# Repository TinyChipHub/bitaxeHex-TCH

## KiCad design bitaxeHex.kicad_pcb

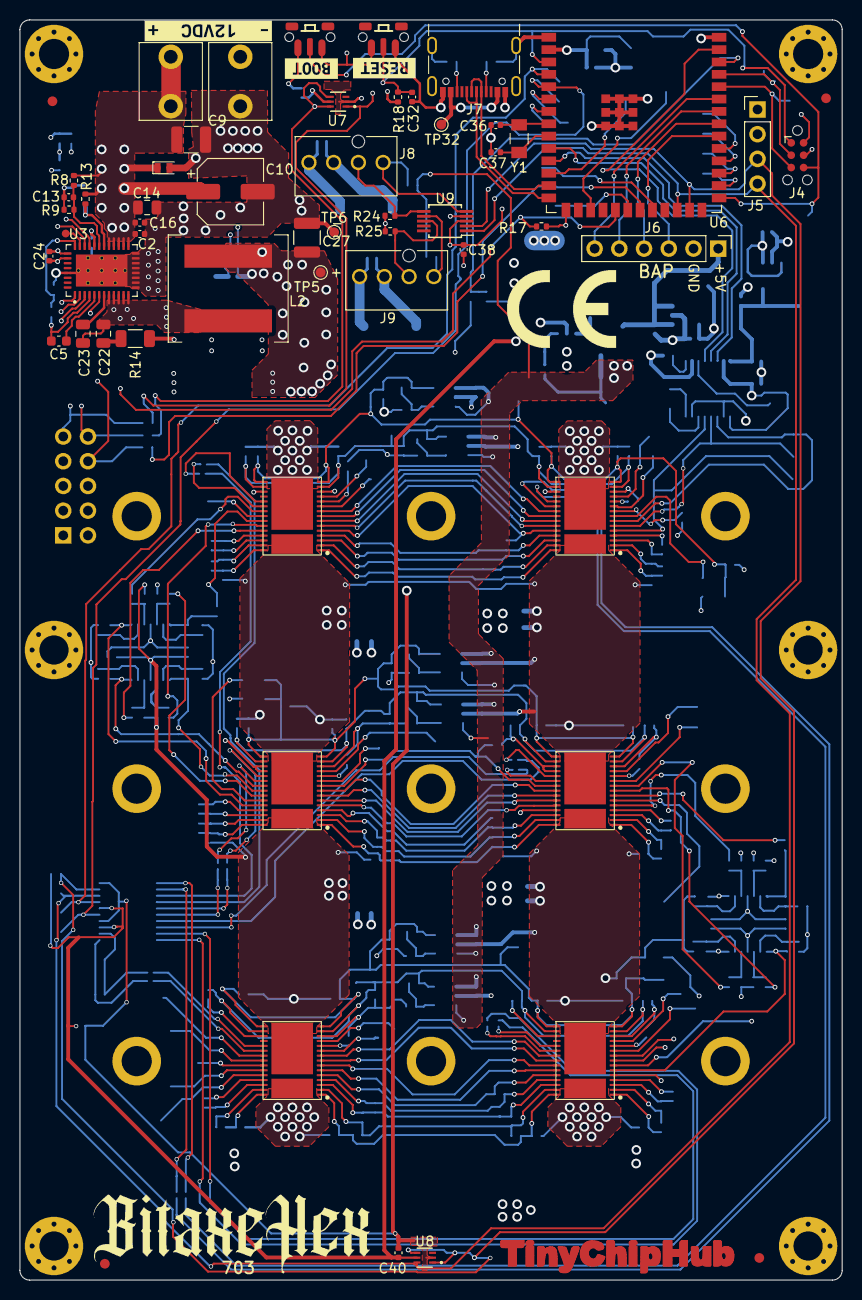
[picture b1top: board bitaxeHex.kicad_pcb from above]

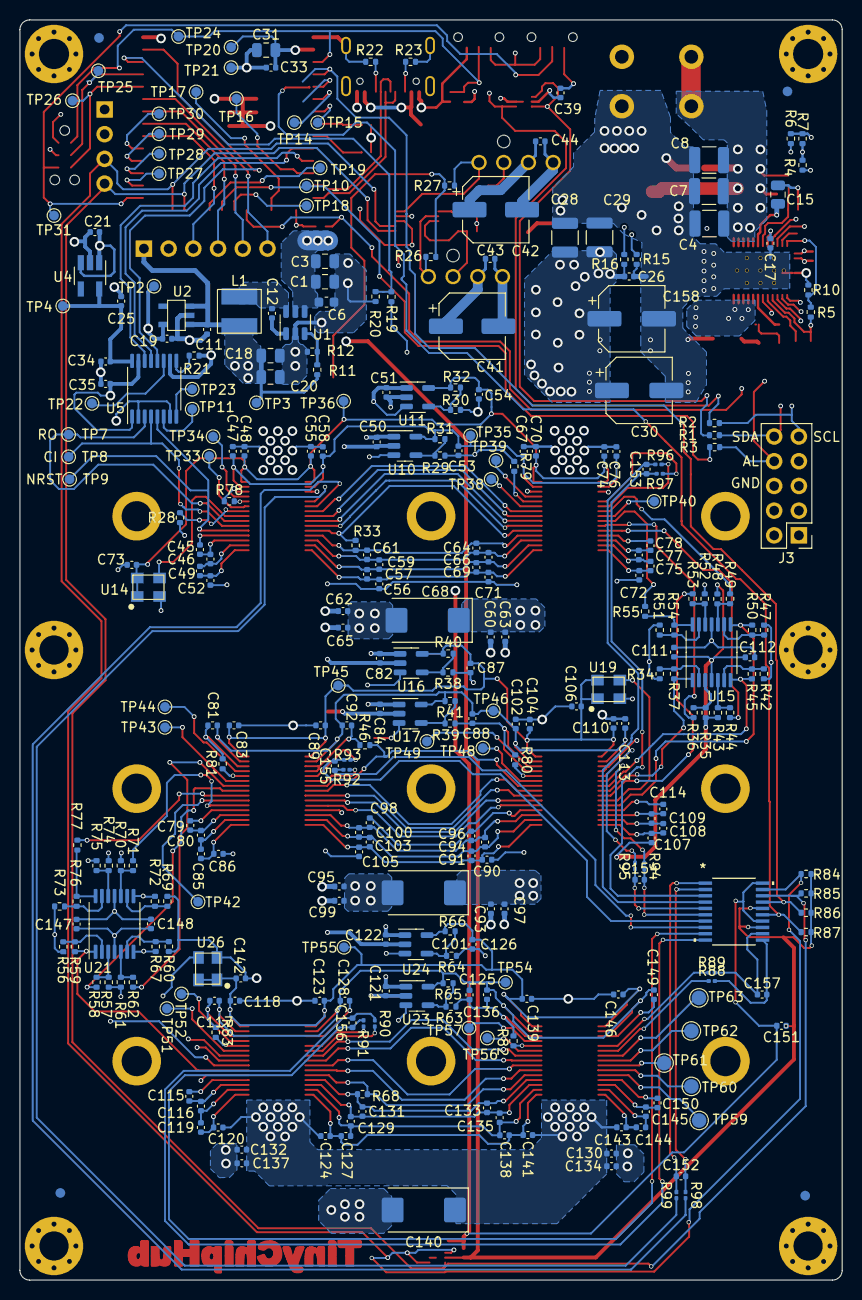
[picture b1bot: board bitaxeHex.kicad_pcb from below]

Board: 4 copper layers, 84.5 x 129.5 mm, 381 parts (306 on the bottom side), 216 nets.

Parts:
C1, C3, C18, C20, C31: 10uF; C_0805_2012Metric
C2: 4.7nF; C_0402_1005Metric
C4, C7, C8, C9: 22uF; C_1210_3225Metric
C5: 1uF; C_0603_1608Metric
C6: 0.1uF; C_0603_1608Metric
C10, C30, C158: 180uF; CP_Elec_6.3x5.9
C11, C19, C21, C25, C32, C45, C46, C47, C48, C49, C52, C53, C54, C55, C56, C57, C58, C59, C61, C63, C64, C65, C66, C67, C69, C70, C71, C72, C74, C75, C76, C77, C78, C79, C80, C81, C83, C85, C86, C87, C88, C89, C90, C91, C92, C94, C96, C97, C98, C99, C100, C102, C103, C104, C105, C107, C108, C109, C110, C112, C113, C114, C115, C116, C117, C118, C119, C120, C123, C124, C125, C126, C127, C128, C129, C131, C133, C134, C135, C136, C137, C138, C139, C141, C143, C144, C145, C146, C148, C149, C150: 1uF; C_0402_1005Metric
C12, C33, C50, C51, C60, C62, C73, C82, C84, C93, C95, C106, C111, C121, C122, C130, C132, C142, C147, C151: 0.1uF; C_0402_1005Metric
C13: 100nF; C_0402_1005Metric
C14, C15: 1uF; C_0805_2012Metric
C16, C26, C152, C153, C154, C155, C156, C157: 2.2nF; C_0402_1005Metric
C17: 4.7uF; C_0402_1005Metric
C22: 1nF; C_0805_2012Metric
C23: 100nF; C_0805_2012Metric
C24: 100pF; C_0402_1005Metric
C27, C28, C29: 47uF; C_1210_3225Metric
C34, C35, C38, C39, C40, C43, C44: 311-3342-1-ND; C_0402_1005Metric
C36, C37: 6.8pF; C_0402_1005Metric
C41, C42: 220uF; CP_Elec_6.3x7.7
C68, C101, C140: 330uF; CP_EIA-7343-31_Kemet-D_Pad2.25x2.55mm_HandSolder
D1: 824045812
FID1, FID2, FID3, FID4, FID5, FID6, FID7, FID8: Fiducial; Fiducial_1mm_Mask2mm
H1, H2, H3, H4, H5, H6: MountingHole; MountingHole_3mm_Pad_Via
H7, H8, H9, H10, H11, H12, H13, H14, H15: HeatsinkMountingHole; 3.1mm_mounting
HS1: Heatsink; hex-heatsink
J1, J2: Conn_01x01; 63862-1
J3: Conn_02x05_Odd_Even; PinHeader_2x05_P2.54mm_Vertical
J4: TC2030-IDC; Tag-Connect_TC2030-IDC-NL_2x03_P1.27mm_Vertical
J5: Conn_01x04; PinHeader_1x04_P2.54mm_Vertical
J6: Conn_01x06; PinHeader_1x06_P2.54mm_Vertical
J7: USB_C_Receptacle_USB2.0; USB_C_Receptacle_GCT_USB4105-xx-A_16P_TopMnt_Horizontal
J8, J9: Conn_01x04; 470531000
L1: 8.2 uH; 74438357082
L2: 680nH; L_Coilcraft_XAL1010-XXX
R1, R2, R3: 0R; R_0402_1005Metric
R4, R5: 17.8K; R_0402_1005Metric
R6, R17, R18, R26, R27, R28, R35, R36, R43, R44, R48, R49, R52, R53, R57, R58, R61, R62, R70, R71, R74, R75: 10k; R_0402_1005Metric
R7: 31.6K; R_0402_1005Metric
R8: 12.7K; R_0402_1005Metric
R9, R16: 1.37K; R_0402_1005Metric
R10: 26.1K; R_0402_1005Metric
R11, R29, R30, R31, R38, R39, R41, R63, R64, R65: 115k; R_0402_1005Metric
R12, R20: 22.1k; R_0402_1005Metric
R13: 10R; R_0402_1005Metric
R14: 1R; R_1206_3216Metric
R15: 49.9R; R_0402_1005Metric
R19: 7.87k; R_0402_1005Metric
R21: 20k; R_0402_1005Metric
R22, R23: 5.1k; R_0402_1005Metric
R24, R25: 5.6k; R_0402_1005Metric
R32, R40, R66: 402k; R_0402_1005Metric
R33, R46, R68: 2k; R_0402_1005Metric
R34, R37, R42, R45, R47, R50, R51, R54, R55, R56, R59, R60, R67, R69, R72, R73, R76, R77, R78, R79, R80, R81, R82, R83: 1k; R_0402_1005Metric
R84, R85, R86, R87: 4.7k; R_0402_1005Metric
R88, R89, R90, R91, R92, R93, R94, R95, R96, R97, R98, R99: 100R; R_0201_0603Metric
SW1, SW2: SWITCH-SPST; TL3340-switch
TP1: TestPoint; TestPoint_Pad_D0.8mm
TP2, TP3, TP4, TP5, TP6, TP7, TP8, TP9, TP10, TP11, TP14, TP15, TP16, TP17, TP18, TP19, TP20, TP21, TP22, TP23, TP24, TP25, TP26, TP27, TP28, TP29, TP30, TP31, TP32, TP33, TP34, TP35, TP36, TP38, TP39, TP40, TP42, TP43, TP44, TP45, TP46, TP48, TP49, TP51, TP52, TP54, TP55, TP56, TP57: TestPoint; TestPoint_Pad_D1.0mm
TP59, TP60, TP61, TP62, TP63: TestPoint; TestPoint_Pad_D1.5mm
U1: LMR54410; SOT-23-6
U2: RT9080-33GJ5
U3: TPS546D24ARVFR; LQFN40-CLIP
U4: MIC5504-MS; SOT-23-5_HandSoldering
U5: SN74AVC4T774; TSSOP-16_4.4x5mm_P0.65mm
U6: ESP32-S3-WROOM-1; ESP32-S3-WROOM-1U
U7, U8: TMP1075; SOT5X3-6_DRL_TEX
U9: EMC2302; MSOP-10_3x3mm_P0.5mm
U10, U11, U16, U17, U23, U24: AP7331; TSOT-23-5
U12, U25, U27, U28: BM1368_mode1; BM1368
U13, U18: BM1368_mode0; BM1368
U14, U19, U26: 25MHz; O 25,0-JO32-B-1V3-1-T1-LF
U15, U21: TLV3544; TSSOP-14_4.4x5mm_P0.65mm
U20: MAX6689UP9A+
Y1: 32.768kHz; SC32S-7PF20PPM
kibuzzard-65356D4E: G***; kibuzzard-65356D4E
kibuzzard-65356D5C: G***; kibuzzard-65356D5C
kibuzzard-65978662: G***; kibuzzard-65978662

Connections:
/1V8: C25.1, C34.2, TP4.1, U4.5 (VOUT), U5.16 (VCCA)
/3V3: C19.1, C21.1, C31.1, C33.1, C35.1, C38.1, C39.1, C40.1, C151.1, J4.2, J5.2, R17.2, R18.1, R24.2, R25.2, R84.2, R85.2, R86.2, R87.2, TP2.1, TP20.1, U2.5 (VOUT), U4.1 (VIN), U4.3 (EN), U5.1 (DIR1), U5.15 (VCCB), U6.2 (3V3), U6.15 (GPIO3/TOUCH3/ADC1_CH2*), U7.5 (V+), U8.5 (V+), U9.3 (VDD), U20.13 (STBY), U20.16 (VCC)
/5V: C11.1, C18.1, C20.1, C50.2, C51.2, C82.2, C84.2, C121.2, C122.2, J6.1, L1.2, R11.1, R26.2, R27.2, TP3.1, U2.1 (VIN), U2.3 (EN), U10.1 (VIN), U10.3 (EN), U11.1 (VIN), U11.3 (EN), U16.1 (VIN), U16.3 (EN), U17.1 (VIN), U17.3 (EN), U23.1 (VIN), U23.3 (EN), U24.1 (VIN), U24.3 (EN)
/BM1368-1/0V8: C47.1, C53.1, C58.1, C67.1, C76.1, R31.2, TP35.1, U10.5 (VOUT), U12.14 (VDDIO_08_0), U12.17 (VDDIO_08_1), U28.14 (VDDIO_08_0), U28.17 (VDDIO_08_1)
/BM1368-1/1V8: C48.1, C54.1, C55.1, C70.1, C73.1, C74.1, R32.1, TP36.1, U11.5 (VOUT), U12.15 (VDDIO_12_0), U12.16 (VDDIO_12_1), U14.1 (EN), U14.4 (VIN), U28.15 (VDDIO_12_0), U28.16 (VDDIO_12_1)
/BM1368-1/BI1: R28.2, U28.9 (BI)
/BM1368-1/BO: R49.1, U12.22 (BO)
/BM1368-1/CLKI1: U14.3 (OUT), U28.8 (CLKI)
/BM1368-1/CO: R36.1, U12.25 (CO)
/BM1368-1/NRSTO: R44.1, U12.26 (NRSTO)
/BM1368-1/RI: R55.1, U12.24 (RI)
/BM1368-1/TEMP_N1: R98.1, U28.21 (TEMP_N)
/BM1368-1/TEMP_N2: R96.1, U12.21 (TEMP_N)
/BM1368-1/TEMP_P1: R99.1, U28.20 (TEMP_P)
/BM1368-1/TEMP_P2: R97.1, U12.20 (TEMP_P)
/BM1368-1/VDD1: C52.2, C56.1, C60.2, C62.2, C63.1, C65.1, C68.1, C71.2, C72.1, C79.1, C81.2, C82.1, C83.2, C84.1, C87.2, C88.2, C89.2, C92.2, C93.1, C95.1, C96.2, C97.2, C98.1, C99.2, C101.2, C102.2, C104.2, C106.2, C110.2, C113.2, C114.2, C147.1, C148.1, R34.2, R38.1, R39.1, R42.2, R46.1, R47.2, R51.2, R74.1, R80.1, R81.1, U12.31 (VDD), U13.4 (VSS), U13.13 (PLL_VSS), U13.18 (VSS), U13.19 (PIN_MODE), U13.27 (VSS), U13.32 (VSS), U16.2 (GND), U17.2 (GND), U18.4 (VSS), U18.13 (PLL_VSS), U18.18 (VSS), U18.19 (PIN_MODE), U18.27 (VSS), U18.32 (VSS), U19.2 (GND), U21.11 (V-), U28.31 (VDD)
/BM1368-2/0V8: C81.1, C88.1, C92.1, C102.1, C113.1, R41.2, TP46.1, U13.14 (VDDIO_08_0), U13.17 (VDDIO_08_1), U17.5 (VOUT), U18.14 (VDDIO_08_0), U18.17 (VDDIO_08_1)
/BM1368-2/1V8: C83.1, C87.1, C89.1, C104.1, C106.1, C110.1, R40.1, TP45.1, U13.15 (VDDIO_12_0), U13.16 (VDDIO_12_1), U16.5 (VOUT), U18.15 (VDDIO_12_0), U18.16 (VDDIO_12_1), U19.1 (EN), U19.4 (VIN)
/BM1368-2/BI2: R50.1, U13.26 (BI), U15.8
/BM1368-2/BO: R71.1, U18.5 (BO)
/BM1368-2/CI2: R37.1, U13.23 (CI), U15.1
/BM1368-2/CLKI2: U13.25 (CLKI), U19.3 (OUT)
/BM1368-2/CO: R58.1, U18.8 (CO)
/BM1368-2/NRSTI2: R45.1, U13.22 (NRSTI), U15.7
/BM1368-2/NRSTO: R62.1, U18.9 (NRSTO)
/BM1368-2/RI: R77.1, U18.7 (RI)
/BM1368-2/RO2: R53.1, U13.24 (RO)
/BM1368-2/TEMP_N3: R94.1, U13.21 (TEMP_N)
/BM1368-2/TEMP_N4: R92.1, U18.21 (TEMP_N)
/BM1368-2/TEMP_P3: R95.1, U13.20 (TEMP_P)
/BM1368-2/TEMP_P4: R93.1, U18.20 (TEMP_P)
/BM1368-2/VDD2: C86.2, C90.1, C93.2, C95.2, C97.1, C99.1, C101.1, C105.2, C107.1, C111.2, C112.2, C115.1, C117.2, C118.2, C121.1, C122.1, C123.2, C125.2, C126.2, C128.2, C130.1, C131.2, C132.1, C133.1, C134.2, C136.2, C137.2, C139.2, C140.2, C142.2, C146.2, C149.2, C150.2, R35.2, R43.1, R48.1, R56.2, R60.2, R63.1, R64.1, R68.1, R69.2, R73.2, R82.1, R83.1, U13.31 (VDD), U15.4 (V+), U18.31 (VDD), U23.2 (GND), U24.2 (GND), U25.4 (VSS), U25.13 (PLL_VSS), U25.18 (VSS), U25.27 (VSS), U25.32 (VSS), U26.2 (GND), U27.4 (VSS), U27.13 (PLL_VSS), U27.18 (VSS), U27.27 (VSS), U27.32 (VSS)
/BM1368-3/0V8: C117.1, C125.1, C128.1, C136.1, C149.1, R65.2, TP54.1, U23.5 (VOUT), U25.14 (VDDIO_08_0), U25.17 (VDDIO_08_1), U27.14 (VDDIO_08_0), U27.17 (VDDIO_08_1)
/BM1368-3/1V8: C118.1, C123.1, C126.1, C139.1, C142.1, C146.1, R66.1, TP55.1, U24.5 (VOUT), U25.15 (VDDIO_12_0), U25.16 (VDDIO_12_1), U26.1 (EN), U26.4 (VIN), U27.15 (VDDIO_12_0), U27.16 (VDDIO_12_1)
/BM1368-3/BI3: R72.1, U21.8, U25.9 (BI)
/BM1368-3/BO3: TP60.1, U27.25 (CO)
/BM1368-3/CI3: R59.1, U21.1, U25.6 (CI)
/BM1368-3/CLKI3: U25.8 (CLKI), U26.3 (OUT)
/BM1368-3/CLKO3: TP62.1, U27.23 (CLKO)
/BM1368-3/CO3: TP63.1, U27.22 (BO)
/BM1368-3/NRSTI3: R67.1, U21.7, U25.5 (NRSTI)
/BM1368-3/NRSTO3: TP59.1, U27.26 (NRSTO)
/BM1368-3/RI3: TP61.1, U27.24 (RI)
/BM1368-3/RO3: R75.1, U25.7 (RO)
/BM1368-3/TEMP_N5: R90.1, U25.21 (TEMP_N)
/BM1368-3/TEMP_N6: R88.1, U27.21 (TEMP_N)
/BM1368-3/TEMP_P5: R91.1, U25.20 (TEMP_P)
/BM1368-3/TEMP_P6: R89.1, U27.20 (TEMP_P)
/CI: TP8.1, U5.4 (A2), U28.6 (CI)
/ESP32/ALERT_TEMP: R86.1, U6.4 (GPIO4/TOUCH4/ADC1_CH3), U20.17 (ALERT)
/ESP32/ASIC_RST: U5.12 (B3), U6.39 (GPIO1/TOUCH1/ADC1_CH0)
/ESP32/EN: C32.1, J4.1, R18.2, SW1.2, TP24.1, U6.3 (EN)
/ESP32/ESP32_RX: U5.14 (B1), U6.11 (GPIO18/U1RXD/ADC2_CH7/CLK_OUT3)
/ESP32/ESP32_TX: U5.13 (B2), U6.10 (GPIO17/U1TXD/ADC2_CH6)
/ESP32/IO0: J4.6, SW2.2, TP31.1, U6.27 (GPIO0/BOOT*)
/ESP32/OVERT_TEMP: R87.1, U6.5 (GPIO5/TOUCH5/ADC1_CH4), U20.15 (OVERT)
/ESP32/P_RX: J4.5, TP26.1, U6.36 (U0RXD/GPIO44/CLK_OUT2)
/ESP32/P_TX: J4.3, TP25.1, U6.37 (U0TXD/GPIO43/CLK_OUT1)
/ESP32/VDD_SAMPLE: R19.1, R20.2, U6.38 (GPIO2/TOUCH2/ADC1_CH1)
/ESP32/XIN32: C36.1, U6.8 (GPIO15/U0RTS/ADC2_CH4/XTAL_32K_P), Y1.1
/ESP32/XOUT32: C37.1, U6.9 (GPIO16/U0CTS/ADC2_CH5/XTAL_32K_NH5), Y1.2
/Fan/FAN1_PWM: J8.4, R27.1, U9.5 (PWM1)
/Fan/FAN1_TACH: J8.3, R24.1, U9.6 (TACH1)
/Fan/FAN2_PWM: J9.4, R26.1, U9.7 (PWM2)
/Fan/FAN2_TACH: J9.3, R25.1, U9.8 (TACH2)
/NRSTI: TP9.1, U5.5 (A3), U28.5 (NRSTI)
/Power/AGND: C13.2, C15.1, R6.1, R7.2, R9.2, R10.2, U3.37 (AGND)
/Power/PGOOD: R17.1, U3.1 (PGD), U6.19 (GPIO11/TOUCH11/ADC2_CH0/FSPID/FSPIIO5/S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)
/Power/PMB_ALRT: J3.8, R3.2, U3.6 (SMB_ALRT)
/Power/PMB_SCL: J3.9, R2.2, U3.3 (PMB_CLK)
/Power/PMB_SDA: J3.10, R1.2, U3.2 (PMB_DATA)
/Power/SW: C22.1, C23.2, L2.1, U3.8 (SW), U3.9 (SW), U3.10 (SW), U3.11 (SW), U3.12 (SW)
/RO: TP7.1, U5.3 (A1), U28.7 (RO)
/SCL: J5.3, R2.1, R84.1, U6.25 (GPIO48/SPICLK_N/SUBSPICLK_N_DIFF), U7.1 (SCL), U8.1 (SCL), U8.4 (A0), U9.2 (SMCLK), U20.19 (SCL)
/SDA: J5.4, R1.1, R85.1, U6.24 (GPIO47/SPICLK_P/SUBSPICLK_P_DIFF), U7.4 (A0), U7.6 (SDA), U8.6 (SDA), U9.1 (SMDATA), U20.18 (SDA)
/SMB_ALRT: R3.1, TP10.1, U6.21 (GPIO13/TOUCH13/ADC2_CH2/FSPIQ/FSPIIO7/S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)
/VDD: C26.1, C27.1, C28.1, C29.1, C30.1, C120.2, C124.1, C130.2, C132.2, C134.1, C137.1, C140.1, C141.2, C143.1, C147.2, C148.2, C158.1, L2.2, R16.1, R19.2, R57.1, R61.1, R70.1, TP5.1, U21.4 (V+), U25.31 (VDD), U27.31 (VDD)
/VIN: C1.1, C2.1, C3.1, C4.1, C6.2, C7.1, C8.1, C9.1, C10.1, C14.1, C16.1, C41.1, C42.1, C43.1, C44.1, D1.1 (I/O), J1.1, J8.2, J9.2, R8.1, R13.1, U1.4 (EN), U1.5 (VIN), U3.21 (PVIN), U3.22 (PVIN), U3.23 (PVIN), U3.24 (PVIN), U3.25 (PVIN)
GND: C1.2, C2.2, C3.2, C4.2, C6.1, C7.2, C8.2, C9.2, C10.2, C11.2, C14.2, C16.2, C17.2, C18.2, C19.2, C20.2, C21.2, C25.2, C26.2, C27.2, C28.2, C29.2, C30.2, C31.2, C32.2, C33.2, C34.1, C35.2, C36.2, C37.2, C38.2, C39.2, C40.2, C41.2, C42.2, C43.2, C44.2, C45.1, C47.2, C48.2, C50.1, C51.1, C53.2, C54.2, C55.2, C58.2, C60.1, C61.2, C62.1, C63.2, C64.1, C65.2, C67.2, C68.2, C70.2, C73.2, C74.2, C76.2, C78.2, C111.1, C112.1, C151.2, C158.2, D1.2 (GND), H1.1, H2.1, J2.1, J3.6, J4.4, J5.1, J6.2, J7.A1 (GND), J7.A12 (GND), J7.B1 (GND), J7.B12 (GND), J7.S1 (SHIELD), J8.1, J9.1, R12.2, R14.2, R15.2, R20.1, R21.1, R22.1, R23.1, R28.1, R29.1, R30.1, R33.1, R52.1, R78.1, R79.1, SW1.1, SW2.1, TP6.1, TP21.1, U1.2 (GND), U2.2 (GND), U3.13 (PGND), U3.14 (PGND), U3.15 (PGND), U3.16 (PGND), U3.17 (PGND), U3.18 (PGND), U3.19 (PGND), U3.20 (PGND), U3.41 (PAD), U4.2 (GND), U5.2 (DIR2), U5.7 (DIR3), U5.10 (GND), U6.1 (GND), U6.40 (GND), U6.41 (GND), U7.2 (GND), U8.2 (GND), U9.4 (GND), U10.2 (GND), U11.2 (GND), U12.4 (VSS), U12.13 (PLL_VSS), U12.18 (VSS), U12.27 (VSS), U12.32 (VSS), U14.2 (GND), U15.11 (V-), U20.14 (N.C.), U20.20 (GND), U28.4 (VSS), U28.13 (PLL_VSS), U28.18 (VSS), U28.27 (VSS), U28.32 (VSS)
unnamed: C22.2, R14.1
unnamed: J6.3, U6.32 (MTCK/GPIO39/CLK_OUT3/SUBSPICS1)
unnamed: J6.4, U6.33 (MTDO/GPIO40/CLK_OUT2)
unnamed: J6.5, U6.34 (MTDI/GPIO41/CLK_OUT1)
unnamed: J6.6, U6.35 (MTMS/GPIO42)
unnamed: J7.A5 (CC1), R22.2
unnamed: J7.B5 (CC2), R23.2
unnamed: J7.A4 (VBUS), J7.A9 (VBUS), J7.B4 (VBUS), J7.B9 (VBUS), TP32.1
unnamed: R54.1, R55.2, U15.14
unnamed: R76.1, R77.2, U21.14
unnamed: C12.2, U1.1 (CB)
unnamed: R11.2, R12.1, U1.3 (FB)
unnamed: C12.1, L1.1, U1.6 (SW)
unnamed: TP1.1, U3.31 (ADRSEL)
unnamed: C15.2, R13.2, U3.26 (AVIN)
unnamed: C23.1, U3.7 (BOOT)
unnamed: C5.1, R4.1, R5.1, U3.4 (BP1V5)
unnamed: C5.2, U3.5 (DRTN)
unnamed: C13.1, R8.2, R9.1, U3.27 (EN/UVLO)
unnamed: C24.2, R15.1, U3.34 (GOSNS)
unnamed: R5.2, R10.1, U3.32 (MSEL1)
unnamed: R6.2, U3.29 (MSEL2)
unnamed: C17.1, U3.28 (VDD5)
unnamed: C24.1, R16.2, U3.33 (VOSNS)
unnamed: R4.2, R7.1, U3.30 (VSEL)
unnamed: TP11.1, U5.6 (A4)
unnamed: TP22.1, U5.11 (B4)
unnamed: TP23.1, U5.8 (DIR4)
unnamed: R21.2, U5.9 (OE)
unnamed: TP14.1, U6.6 (GPIO6/TOUCH6/ADC1_CH5)
unnamed: TP15.1, U6.7 (GPIO7/TOUCH7/ADC1_CH6)
unnamed: TP16.1, U6.12 (GPIO8/TOUCH8/ADC1_CH7/SUBSPICS1)
unnamed: TP17.1, U6.17 (GPIO9/TOUCH9/ADC1_CH8/FSPIHD/SUBSPIHD)
unnamed: TP18.1, U6.20 (GPIO12/TOUCH12/ADC2_CH1/FSPICLK/FSPIIO6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)
unnamed: TP19.1, U6.22 (GPIO14/TOUCH14/ADC2_CH3/FSPIWP/FSPIDQS/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)
unnamed: J7.A7 (D-), J7.B7 (D-), U6.13 (GPIO19/U1RTS/ADC2_CH8/CLK_OUT2/USB_D-)
unnamed: J7.A6 (D+), J7.B6 (D+), U6.14 (GPIO20/U1CTS/ADC2_CH9/CLK_OUT1/USB_D+)
unnamed: TP30.1, U6.31 (GPIO38/FSPIWP/SUBSPIWP)
unnamed: TP29.1, U6.30 (SPIDQS/GPIO37/FSPIQ/SUBSPIQ)
unnamed: TP27.1, U6.28 (SPIIO6/GPIO35/FSPID/SUBSPID)
unnamed: TP28.1, U6.29 (SPIIO7/GPIO36/FSPICLK/SUBSPICLK)
unnamed: R29.2, R31.1, U10.4 (ADJ)
unnamed: R30.2, R32.2, U11.4 (ADJ)
unnamed: U12.9 (BI), U28.22 (BO)
unnamed: U12.6 (CI), U28.25 (CO)
unnamed: U12.8 (CLKI), U28.23 (CLKO)
unnamed: TP40.1, U12.23 (CLKO)
unnamed: TP39.1, U12.12 (INV_CLKO)
unnamed: R79.2, U12.11 (LITE_PAD)
unnamed: R33.2, U12.5 (NRSTI), U28.26 (NRSTO)
unnamed: U12.7 (RO), U28.24 (RI)
unnamed: TP38.1, U12.10 (ROSC_SEL)
unnamed: C59.2, C61.1, C64.2, C66.1, U12.3 (VDD1_0), U28.28 (VDD1_1)
unnamed: C77.2, C78.1, U12.28 (VDD1_1)
unnamed: C57.2, C59.1, C66.2, C69.1, U12.2 (VDD2_0), U28.29 (VDD2_1)
unnamed: C75.2, C77.1, U12.29 (VDD2_1)
unnamed: C56.2, C57.1, C69.2, C71.1, U12.1 (VDD3_0), U28.30 (VDD3_1)
unnamed: C72.2, C75.1, U12.30 (VDD3_1)
unnamed: U13.5 (BO), U18.26 (BI)
unnamed: U13.6 (CLKO), U18.25 (CLKI)
unnamed: U13.8 (CO), U18.23 (CI)
unnamed: TP49.1, U13.12 (INV_CLKO)
unnamed: R80.2, U13.11 (LITE_PAD)
unnamed: R46.2, U13.9 (NRSTO), U18.22 (NRSTI)
unnamed: U13.7 (RI), U18.24 (RO)
unnamed: TP48.1, U13.10 (ROSC_SEL)
unnamed: C94.2, C96.1, C98.2, C100.1, U13.3 (VDD1_0), U18.28 (VDD1_1)
unnamed: C109.2, C114.1, U13.28 (VDD1_1)
unnamed: C91.2, C94.1, C100.2, C103.1, U13.2 (VDD2_0), U18.29 (VDD2_1)
unnamed: C108.2, C109.1, U13.29 (VDD2_1)
unnamed: C90.2, C91.1, C103.2, C105.1, U13.1 (VDD3_0), U18.30 (VDD3_1)
unnamed: C107.2, C108.1, U13.30 (VDD3_1)
unnamed: R35.1, R36.2, U15.3 (+)
unnamed: R34.1, R37.2, U15.2 (-)
unnamed: R43.2, R44.2, U15.5 (+)
unnamed: R42.1, R45.2, U15.6 (-)
unnamed: R48.2, R49.2, U15.10 (+)
unnamed: R47.1, R50.2, U15.9 (-)
unnamed: R52.2, R53.2, U15.12 (+)
unnamed: R51.1, R54.2, U15.13 (-)
unnamed: R38.2, R40.2, U16.4 (ADJ)
unnamed: R39.2, R41.1, U17.4 (ADJ)
unnamed: TP42.1, U18.6 (CLKO)
unnamed: TP44.1, U18.12 (INV_CLKO)
unnamed: R81.2, U18.11 (LITE_PAD)
unnamed: TP43.1, U18.10 (ROSC_SEL)
unnamed: C79.2, C80.1, U18.3 (VDD1_0)
unnamed: C80.2, C85.1, U18.2 (VDD2_0)
unnamed: C85.2, C86.1, U18.1 (VDD3_0)
unnamed: C152.2, R98.2, U20.2 (DXN1)
unnamed: C153.2, R96.2, U20.4 (DXN2)
unnamed: C154.2, R94.2, U20.6 (DXN3)
unnamed: C155.2, R92.2, U20.8 (DXN4)
unnamed: C156.2, R90.2, U20.10 (DXN5)
unnamed: C157.2, R88.2, U20.11 (DXN6)
unnamed: C152.1, R99.2, U20.1 (DXP1)
unnamed: C153.1, R97.2, U20.3 (DXP2)
unnamed: C154.1, R95.2, U20.5 (DXP3)
unnamed: C155.1, R93.2, U20.7 (DXP4)
unnamed: C156.1, R91.2, U20.9 (DXP5)
unnamed: C157.1, R89.2, U20.12 (DXP6)
unnamed: R57.2, R58.2, U21.3 (+)
unnamed: R56.1, R59.2, U21.2 (-)
unnamed: R61.2, R62.2, U21.5 (+)
unnamed: R60.1, R67.2, U21.6 (-)
unnamed: R70.2, R71.2, U21.10 (+)
unnamed: R69.1, R72.2, U21.9 (-)
unnamed: R74.2, R75.2, U21.12 (+)
unnamed: R73.1, R76.2, U21.13 (-)
unnamed: R63.2, R65.1, U23.4 (ADJ)
unnamed: R64.2, R66.2, U24.4 (ADJ)
unnamed: U25.22 (BO), U27.9 (BI)
unnamed: U25.23 (CLKO), U27.8 (CLKI)
unnamed: U25.25 (CO), U27.6 (CI)
unnamed: TP52.1, U25.12 (INV_CLKO)
unnamed: R83.2, U25.11 (LITE_PAD)
unnamed: R68.2, U25.26 (NRSTO), U27.5 (NRSTI)
unnamed: U25.24 (RI), U27.7 (RO)
unnamed: TP51.1, U25.10 (ROSC_SEL)
unnamed: C115.2, C116.1, U25.3 (VDD1_0)
unnamed: C129.2, C131.1, C133.2, C135.1, U25.28 (VDD1_1), U27.3 (VDD1_0)
unnamed: C116.2, C119.1, U25.2 (VDD2_0)
unnamed: C127.2, C129.1, C135.2, C138.1, U25.29 (VDD2_1), U27.2 (VDD2_0)
unnamed: C119.2, C120.1, U25.1 (VDD3_0)
unnamed: C124.2, C127.1, C138.2, C141.1, U25.30 (VDD3_1), U27.1 (VDD3_0)
unnamed: TP57.1, U27.12 (INV_CLKO)
unnamed: R82.2, U27.11 (LITE_PAD)
unnamed: TP56.1, U27.10 (ROSC_SEL)
unnamed: C145.2, C150.1, U27.28 (VDD1_1)
unnamed: C144.2, C145.1, U27.29 (VDD2_1)
unnamed: C143.2, C144.1, U27.30 (VDD3_1)
unnamed: TP34.1, U28.12 (INV_CLKO)
unnamed: R78.2, U28.11 (LITE_PAD)
unnamed: TP33.1, U28.10 (ROSC_SEL)
unnamed: C45.2, C46.1, U28.3 (VDD1_0)
unnamed: C46.2, C49.1, U28.2 (VDD2_0)
unnamed: C49.2, C52.1, U28.1 (VDD3_0)

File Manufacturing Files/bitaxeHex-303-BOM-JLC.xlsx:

Designator | Comment | Footprint | DK | PARTNO
C1, C3, C18, C20, C31 | 10uF | Capacitor_SMD:C_0805_2012Metric | 490-18664-1-ND | GRM21BR61H106ME43L
C2 | 4.7nF | Capacitor_SMD:C_0402_1005Metric | 490-1309-1-ND | GRM155R71E472KA01D
C4, C7, C8, C9 | 22uF | Capacitor_SMD:C_1210_3225Metric | 490-3889-1-ND | GRM32ER61E226KE15L
C5 | 1uF | Capacitor_SMD:C_0603_1608Metric | 490-1550-1-ND | GRM188R60J105KA01D
C6 | 0.1uF | Capacitor_SMD:C_0603_1608Metric | 478-KGM15BR71H104KTCT-ND | KGM15BR71H104KT
C10, C30 | 180uF | Capacitor_SMD:CP_Elec_6.3x5.9 | P16479CT-ND | 16SVPF180M
C11, C19, C21, C25, C32, C45, C46, C47, C48, C49, C52, C53, C54, C55, C56, C57,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 | 1uF | Capacitor_SMD:C_0402_1005Metric | 587-5514-1-ND | EMK105BJ105MV-F
C12, C33, C50, C51, C60, C62, C73, C82, C84, C93, C95, C106, C111, C121, C122, 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 | 0.1uF | Capacitor_SMD:C_0402_1005Metric | 478-KGM05AR71C104KHCT-ND | KGM05AR71C104KH
C13 | 100nF | Capacitor_SMD:C_0402_1005Metric | 490-6321-1-ND | GRM155R71A104KA01D
C14, C15 | 1uF | Capacitor_SMD:C_0805_2012Metric | 587-1291-1-ND | TMK212BJ105KG-T
C16, C26 | 2.2nF | Capacitor_SMD:C_0402_1005Metric | 490-8257-1-ND | GRM155R61H222KA01D
C17 | 4.7uF | Capacitor_SMD:C_0402_1005Metric | 490-14306-1-ND | GRM155R61A475MEAAD
C22 | 1nF | Capacitor_SMD:C_0805_2012Metric | 311-1127-1-ND | CC0805KRX7R9BB102
C23 | 100nF | Capacitor_SMD:C_0805_2012Metric | 478-KGM21NR71E104KTCT-ND | KGM21NR71E104KT
C24 | 100pF | Capacitor_SMD:C_0402_1005Metric | 732-7431-1-ND | 885012005013
C27, C28, C29 | 47uF | Capacitor_SMD:C_1210_3225Metric | 490-6539-1-ND | GRM32ER61C476KE15L
C34, C35, C38, C39, C40, C43, C44 | 311-3342-1-ND | Capacitor_SMD:C_0402_1005Metric | 478-KGM05AR71C104KHCT-ND | KGM05AR71C104KH
C41, C42 | 220uF | Capacitor_SMD:CP_Elec_6.3x7.7 | 732-8422-1-ND | 865080345012
C68, C101, C140 | 330uF | Capacitor_Tantalum_SMD:CP_EIA-7343-31_Kemet-D_Pad2.25x2.55mm_HandSolder | 718-1028-1-ND | 293D337X9010E2TE3
R1, R2, R3 | 0R | Resistor_SMD:R_0402_1005Metric | 311-0.0JRCT-ND | RC0402JR-070RL
R4, R5 | 17.8K | Resistor_SMD:R_0402_1005Metric | RMCF0402FT17K8CT-ND | RMCF0402FT17K8
R6 | 10K | Resistor_SMD:R_0402_1005Metric | RMCF0402FT10K0CT-ND | RMCF0402FT10K0
R7 | 31.6K | Resistor_SMD:R_0402_1005Metric | YAG3115CT-ND | RC0402FR-0731K6L
R8 | 12.7K | Resistor_SMD:R_0402_1005Metric | YAG2964CT-ND | RC0402FR-0712K7L
R9, R16 | 1.37K | Resistor_SMD:R_0402_1005Metric | YAG3035CT-ND | RC0402FR-071K37L
R10 | 26.1K | Resistor_SMD:R_0402_1005Metric | 311-26.1KLRCT-ND | RC0402FR-0726K1L
R11, R29, R30, R31, R38, R39, R41, R63, R64, R65 | 115k | Resistor_SMD:R_0402_1005Metric | YAG2956CT-ND | RC0402FR-07115KL
R12, R20 | 22.1k | Resistor_SMD:R_0402_1005Metric | 311-22.1KLRCT-ND | RC0402FR-0722K1L
R13 | 10R | Resistor_SMD:R_0402_1005Metric | 311-10.0LRCT-ND | RC0402FR-0710RL
R14 | 1R | Resistor_SMD:R_1206_3216Metric | CSR1206FT1R00CT-ND | CSR1206FT1R00
R15 | 49.9R | Resistor_SMD:R_0402_1005Metric | 311-49.9LRCT-ND | RC0402FR-0749R9L
R17, R18, R26, R27, R28, R35, R36, R43, R44, R48, R49, R52, R53, R57, R58, R61,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 | 10k | Resistor_SMD:R_0402_1005Metric | 311-10KJRCT-ND | RC0402JR-0710KL
R19 | 7.87k | Resistor_SMD:R_0402_1005Metric | 311-7.87KLRCT-ND | RC0402FR-077K87L
R21 | 20k | Resistor_SMD:R_0402_1005Metric | 311-20.0KLRCT-ND | RC0402FR-0720KL
R22, R23 | 5.1k | Resistor_SMD:R_0402_1005Metric | 13-RC0402FR-135K1LCT-ND | RC0402FR-135K1L
R24, R25 | 5.6k | Resistor_SMD:R_0402_1005Metric | 13-RC0402FR-135K6LCT-ND | RC0402FR-135K6L
R32, R40, R66 | 402K | Resistor_SMD:R_0402_1005Metric | YAG3151CT-ND | RC0402FR-07402KL
R33, R46, R68 | 2k | Resistor_SMD:R_0402_1005Metric | YAG2303CT-ND | RT0402BRD072KL
R34, R37, R42, R45, R47, R50, R51, R54, R55, R56, R59, R60, R67, R69, R72, R73,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 | 1k | Resistor_SMD:R_0402_1005Metric | 311-1.00KLRCT-ND | RC0402FR-071KL
J1, J2 | Screw Terminal | bitaxe:7771-screw-terminal | 36-7771-ND | 36-7771
J3 | Conn_02x05_Odd_Even | Connector_PinHeader_2.54mm:PinHeader_2x05_P2.54mm_Vertical
J5 | Conn_01x04
J6 | Conn_01x06 | Connector_PinHeader_2.54mm:PinHeader_1x06_P2.54mm_Vertical
J7 | USB_C_Receptacle_USB2.0 | Connector_USB:USB_C_Receptacle_GCT_USB4105-xx-A_16P_TopMnt_Horizontal | 2073-USB4105-GF-ACT-ND | USB4105-GF-A
J8, J9 | Conn_01x04 | bitaxe:470531000 | WM4330-ND | 470531000
L1 | 8.2 uH | bitaxe:74438357082 | 732-11745-1-ND | 78438357082
L2 | 680nH | Inductor_SMD:L_Coilcraft_XAL1010-XXX | 2457-XAL1010-681MED-ND | XAL1010-681MED
SW1, SW2 | SWITCH-SPST | bitaxe:TL3340-switch | EG4627CT-ND | TL3340AF160QG
U1 | LMR54410 | Package_TO_SOT_SMD:SOT-23-6 | 296-LMR54410DBVRCT-ND | LMR54410FDBVR
U2 | RT9080-33GJ5 | bitaxe:RT9080-33GJ5 | 1028-1509-1-ND | RT9080-33GJ5
U3 | TPS546D24ARVFR | bitaxe:LQFN40-CLIP | 296-TPS546D24ARVFRCT-ND | TPS546D24ARVFR
U4 | MIC5504 | Package_TO_SOT_SMD:SOT-23-5_HandSoldering | 576-4879-1-ND | MIC5504-1.8YM5-TR
U5 | SN74AVC4T774 | Package_SO:TSSOP-16_4.4x5mm_P0.65mm | 296-24739-1-ND | SN74AVC4T774PWR
U6 | ESP32-S3-WROOM-1 | bitaxe:ESP32-S3-WROOM-1U | 1965-ESP32-S3-WROOM-1U-N16R8CT-ND | ESP32-S3-WROOM-1U-N16R8
U7, U8 | TMP1075 | bitaxe:SOT5X3-6_DRL_TEX | 296-TMP1075NDRLRCT-ND | TMP1075NDRLR
U9 | EMC2302 | Package_SO:MSOP-10_3x3mm_P0.5mm | EMC2302-2-AIZL-CT-ND | EMC2302-2-AIZL-TR
U10, U11, U16, U17, U23, U24 | AP7331 | Package_TO_SOT_SMD:TSOT-23-5 | AP7331-WG-7DICT-ND | AP7331-WG-7
U12, U13, U22, U25 | BM1366_mode1 | bitaxe:BM1366
U14, U19, U26 | 25MHz | bitaxe:O 25,0-JO32-B-1V3-1-T1-LF | 1908-O250-JO32-B-1V3-1-T1-LFCT-ND | O 25,0-JO32-B-1V3-1-T1-LF
U15, U21 | TLV3544 | Package_SO:TSSOP-14_4.4x5mm_P0.65mm | 296-45352-1-ND | TLV3544IPWR
U18, U20 | BM1366_mode0 | bitaxe:BM1366
D1 | C26174720 | DFN1610-2L | 824045812

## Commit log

2024-08-10 Adding BM1368 symbol and footprint into branch
2024-08-11 Rearrange parts to fit water cooling
2024-08-11 Finalized 303 production files
2024-08-11 Adding BM1368 footprint and symbol into project
2024-08-12 minor update
2024-08-12 Add special version for OSMU
2024-08-12 update gerbers files for OSMU version
2024-08-12 finish sch rearrange for BM1368 chain
2024-08-12 Adding temperature monitoring
2024-08-13 sch update done
2024-08-13 Finish routing
2024-08-14 Upload 3d model for MAX6689
2024-08-15 mark DNP issue
2024-09-05 Add Logo
2024-09-07 Add TVS protection to avoid sudden current which may damage the TPS power regulator
2024-09-08 minor
2024-09-08 Add CE logo on it
2024-09-09 Reset to 1V8/0V8 setting
2024-09-22 Add resisters for MAX6689
2024-09-22 Reset to 1V8
2024-09-22 init push for GammaHex
2024-10-10 Add tvs to 303
2025-03-10 upgrade board version to 703
